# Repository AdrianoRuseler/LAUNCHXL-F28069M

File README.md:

# LAUNCHXL-F28069M

## C2000 Delfino MCUs F28069M LaunchPad Development Kit 
http://www.ti.com/tool/LAUNCHXL-F28069M

## TMS320F28069M
http://www.ti.com/product/TMS320F28069M/technicaldocuments

## Code Composer Studio IDE 
http://www.ti.com/tool/ccstudio

## controlSUITE 
http://www.ti.com/tool/controlsuite

## Wiki
https://aws.adrianoruseler.com/wiki/index.php/LAUNCHXL-F28069M

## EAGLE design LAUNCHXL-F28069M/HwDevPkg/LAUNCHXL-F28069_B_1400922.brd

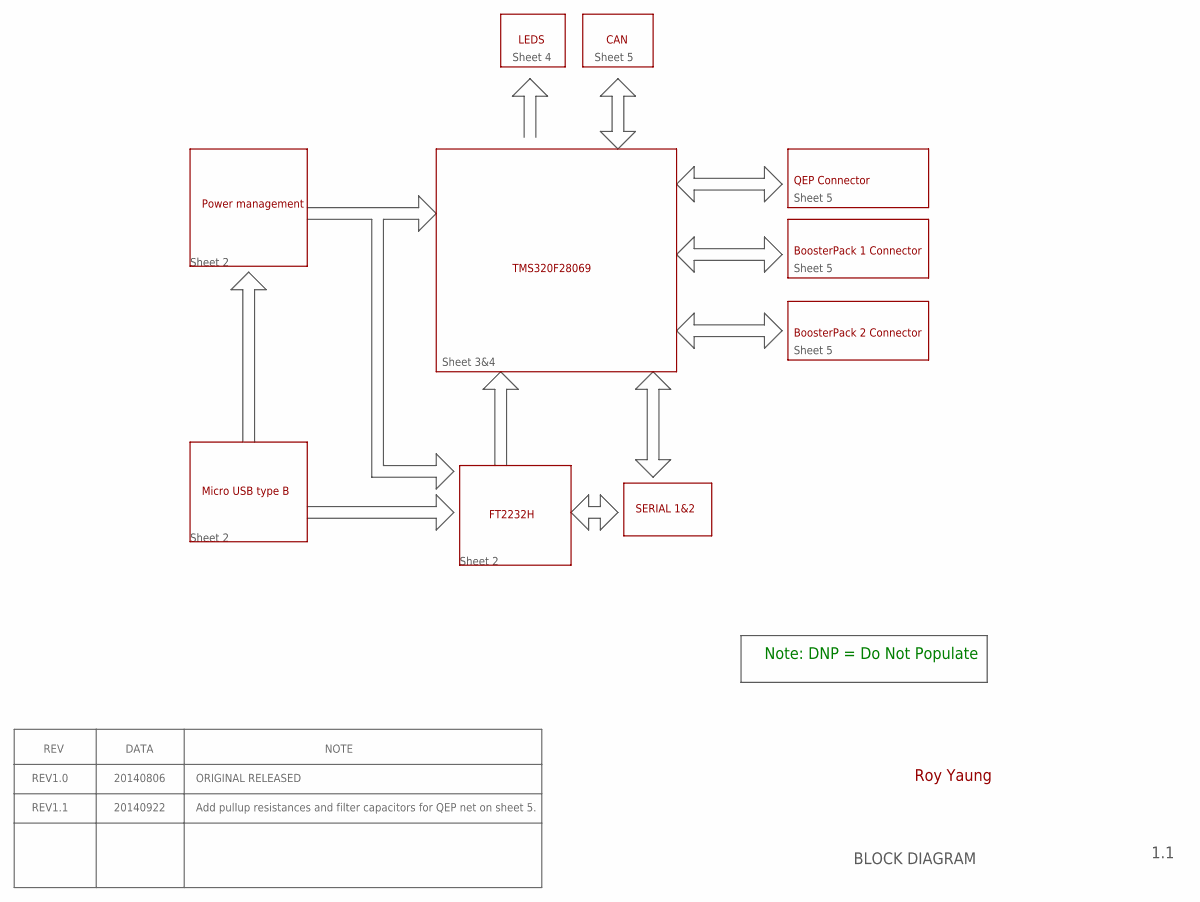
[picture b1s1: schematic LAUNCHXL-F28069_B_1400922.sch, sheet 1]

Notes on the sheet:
1.1
BLOCK DIAGRAM
Power management
Micro USB type B
FT2232H
TMS320F28069
BoosterPack 1 Connector
LEDS
CAN
SERIAL 1&2
Sheet 2
Sheet 3&4
BoosterPack 2 Connector
QEP Connector
Note: DNP = Do Not Populate
Roy Yaung
Sheet 5
Sheet 4
REV
DATA
NOTE
REV1.0
REV1.1
20140806
20140922
ORIGINAL RELEASED
Add pullup resistances and filter capacitors for QEP net on sheet 5.

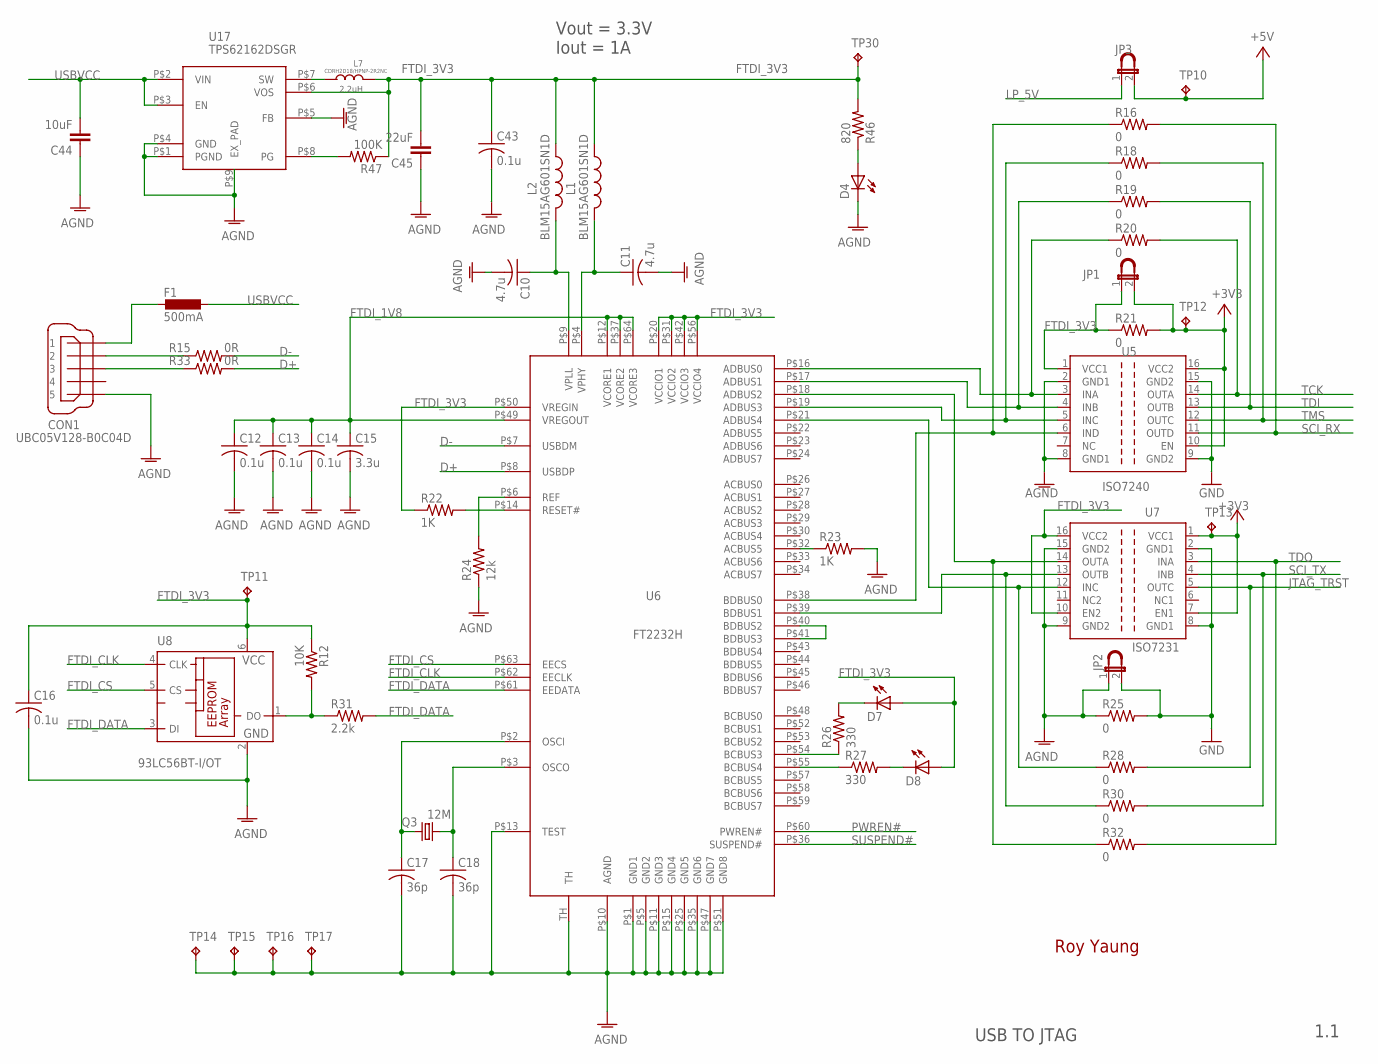
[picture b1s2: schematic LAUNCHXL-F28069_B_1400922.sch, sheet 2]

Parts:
C10, C11: 4.7u; C0402
C12, C13, C14, C16, C43: 0.1u; C0402
C15: 3.3u; C0402
C17, C18: 36p; C0402
C44: 10uF; SPARKFUN_1210
C45: 22uF; SPARKFUN_1210
CON1: UBC05V128-B0C04D; 32005-201
D4, D7, D8: LEDCHIP-LED0603; CHIP-LED0603
F1: 500mA; L1812
JP1, JP2, JP3: JP1ENORM; JP1
L1, L2: BLM15AG601SN1D; R0402
L7: 2.2uH; INDUCT-3.2*3.2
Q3: 12M; HC49UP
R12: 10K; R0402
R15, R33: 0R; R0402
R16, R18, R19, R20, R21, R25, R28, R30, R32: 0; R1206
R22, R23: 1K; R0402
R24: 12k; R0402
R26, R27: 330; R0402
R31: 2.2k; R0402
R46: 820; R0402
R47: 100K; R0402
TP10, TP11, TP12, TP13, TP14, TP15, TP16, TP17, TP30: TESTPAD_TPB1,27; TESTPAD_B1,27
U5: ISO7240; SO-16DW
U6: FT2232H; QFN64
U7: ISO7231; SO-16DW
U8: 93LC56BT-I/OT; SOT23-6
U17: TPS62162DSGR; TI_DSG8
U$9, U$10, U$11: ROY_JUMPER

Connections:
+3V3: JP1.2, R21.2, TP12.TP, TP13.TP, U5.10 (EN), U5.16 (VCC2), U7.1 (VCC1), U7.7 (EN1); also elsewhere on the board
+5V: JP3.2, TP10.TP; also elsewhere on the board
AGND: C10.2, C11.2, C12.2, C13.2, C14.2, C15.2, C16.2, C17.2, C18.2, C43.2, C44.1, C45.1, CON1.5, D4.C, JP2.1, R23.2, R24.1, R25.1, TP14.TP, TP15.TP, TP16.TP, TP17.TP, U5.2 (GND1), U5.8 (GND1), U6.P$1 (GND1), U6.P$5 (GND2), U6.P$10 (AGND), U6.P$11 (GND3), U6.P$13 (TEST), U6.P$15 (GND4), U6.P$25 (GND5), U6.P$35 (GND6), U6.P$47 (GND7), U6.P$51 (GND8), U6.TH, U7.9 (GND2), U7.15 (GND2), U8.2 (GND), U17.P$1 (PGND), U17.P$4 (GND), U17.P$5 (FB), U17.P$9 (EX_PAD)
D+: R33.2, U6.P$8 (USBDP)
D-: R15.2, U6.P$7 (USBDM)
FTDI_1V8: C12.1, C13.1, C14.1, C15.1, U6.P$12 (VCORE1), U6.P$37 (VCORE2), U6.P$49 (VREGOUT), U6.P$64 (VCORE3)
FTDI_3V3: C16.1, C43.1, C45.2, D7.A, D8.A, JP1.1, L1.1, L2.1, L7.P$1 (1), R12.1, R21.1, R22.1, R46.2, R47.1, TP11.TP, TP30.TP, U5.1 (VCC1), U6.P$20 (VCCIO1), U6.P$31 (VCCIO2), U6.P$42 (VCCIO3), U6.P$50 (VREGIN), U6.P$56 (VCCIO4), U7.10 (EN2), U7.16 (VCC2), U8.6 (VCC), U17.P$6 (VOS)
FTDI_CLK: U6.P$62 (EECLK), U8.4 (CLK)
FTDI_CS: U6.P$63 (EECS), U8.5 (CS)
FTDI_DATA: R31.2, U6.P$61 (EEDATA), U8.3 (DI)
GND: JP2.2, R25.2, U5.9 (GND2), U5.15 (GND2), U7.2 (GND1), U7.8 (GND1); also elsewhere on the board
JTAG_TRST: R28.2, U7.5 (OUTC); also elsewhere on the board
LP_5V: JP3.1; also elsewhere on the board
unnamed: R20.1, U5.3 (INA), U6.P$16 (ADBUS0)
unnamed: C17.1, Q3.1, U6.P$2 (OSCI)
unnamed: R19.1, U5.4 (INB), U6.P$17 (ADBUS1)
unnamed: R32.1, U6.P$18 (ADBUS2), U7.14 (OUTA)
unnamed: R18.1, U5.5 (INC), U6.P$19 (ADBUS3)
unnamed: C18.1, Q3.2, U6.P$3 (OSCO)
unnamed: R12.2, R31.1, U8.1 (DO)
unnamed: R28.1, U6.P$21 (ADBUS4), U7.12 (INC)
unnamed: R23.1, U6.P$32 (ACBUS5)
unnamed: U6.P$40 (BDBUS2), U6.P$41 (BDBUS3)
unnamed: R16.1, U5.6 (IND), U6.P$38 (BDBUS0)
unnamed: R24.2, U6.P$6 (REF)
unnamed: R26.1, U6.P$54 (BCBUS3)
unnamed: C11.1, L1.2, U6.P$4 (VPHY)
unnamed: R30.1, U6.P$39 (BDBUS1), U7.13 (OUTB)
unnamed: R27.1, U6.P$55 (BCBUS4)
unnamed: D7.C, R26.2
unnamed: D8.C, R27.2
unnamed: C10.1, L2.2, U6.P$9 (VPLL)
unnamed: R22.2, U6.P$14 (RESET#)
unnamed: CON1.2, R15.1
unnamed: CON1.3, R33.1
unnamed: D4.A, R46.1
unnamed: R47.2, U17.P$8 (PG)
unnamed: L7.P$2 (2), U17.P$7 (SW)
PWREN#: U6.P$60 (PWREN#)
SCI_RX: R16.2, U5.11 (OUTD); also elsewhere on the board
SCI_TX: R30.2, U7.4 (INB); also elsewhere on the board
SUSPEND#: U6.P$36 (SUSPEND#)
TCK: R20.2, U5.14 (OUTA); also elsewhere on the board
TDI: R19.2, U5.13 (OUTB); also elsewhere on the board
TDO: R32.2, U7.3 (INA); also elsewhere on the board
TMS: R18.2, U5.12 (OUTC); also elsewhere on the board
USBVCC: C44.2, F1.1, U17.P$2 (VIN), U17.P$3 (EN)
XUSB: CON1.1, F1.2

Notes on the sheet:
1.1
USB TO JTAG
Roy Yaung
Vout = 3.3V
Iout = 1A
CDRH2D18/HPNP-2R2NC

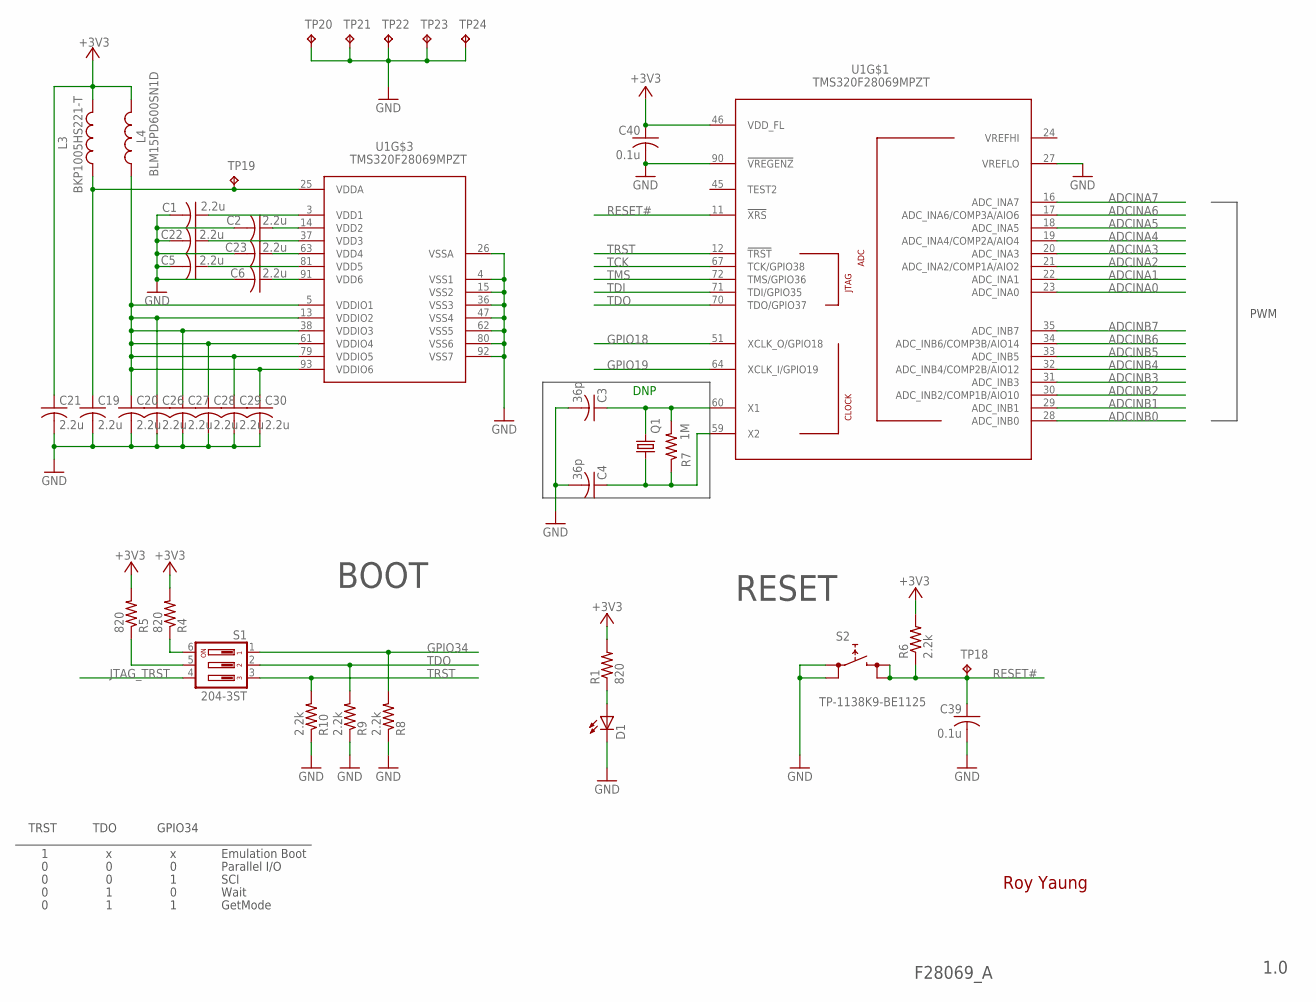
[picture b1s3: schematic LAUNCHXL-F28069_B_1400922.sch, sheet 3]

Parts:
C1, C2, C5, C6, C19, C20, C21, C22, C23, C26, C27, C28, C29, C30: 2.2u; C0402
C3, C4: 36p; C0402
C39, C40: 0.1u; C0402
D1: LEDCHIP-LED0603; CHIP-LED0603
L3: BKP1005HS221-T; R0402
L4: BLM15PD600SN1D; R0402
Q1: CRYSTALHC49S; HC49/S
R1, R4, R5: 820; R0402
R6, R8, R9, R10: 2.2k; R0402
R7: 1M; R0402
S1: 204-3ST; CTS-219-03
S2: TP-1138K9-BE1125; FSMJSMA
TP18, TP19, TP20, TP21, TP22, TP23, TP24: TESTPAD_TPB1,27; TESTPAD_B1,27
U1: TMS320F28069MPZT; PQFP100

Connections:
+3V3: C21.1, C40.1, L3.2, L4.2, R1.2, R4.2, R5.2, R6.2, U1.46 (VDD_FL); also elsewhere on the board
ADCINA0: U1.23 (ADC_INA0); also elsewhere on the board
ADCINA1: U1.22 (ADC_INA1); also elsewhere on the board
ADCINA2: U1.21 (ADC_INA2/COMP1A/AIO2); also elsewhere on the board
ADCINA3: U1.20 (ADC_INA3); also elsewhere on the board
ADCINA4: U1.19 (ADC_INA4/COMP2A/AIO4); also elsewhere on the board
ADCINA5: U1.18 (ADC_INA5); also elsewhere on the board
ADCINA6: U1.17 (ADC_INA6/COMP3A/AIO6); also elsewhere on the board
ADCINA7: U1.16 (ADC_INA7); also elsewhere on the board
ADCINB0: U1.28 (ADC_INB0); also elsewhere on the board
ADCINB1: U1.29 (ADC_INB1); also elsewhere on the board
ADCINB2: U1.30 (ADC_INB2/COMP1B/AIO10); also elsewhere on the board
ADCINB3: U1.31 (ADC_INB3); also elsewhere on the board
ADCINB4: U1.32 (ADC_INB4/COMP2B/AIO12); also elsewhere on the board
ADCINB5: U1.33 (ADC_INB5); also elsewhere on the board
ADCINB6: U1.34 (ADC_INB6/COMP3B/AIO14); also elsewhere on the board
ADCINB7: U1.35 (ADC_INB7); also elsewhere on the board
GND: C1.2, C2.2, C3.2, C4.2, C5.2, C6.2, C19.2, C20.2, C21.2, C22.2, C23.2, C26.2, C27.2, C28.2, C29.2, C30.2, C39.2, C40.2, D1.C, R8.1, R9.1, R10.1, S2.P$1 (0), S2.P$2 (0), TP20.TP, TP21.TP, TP22.TP, TP23.TP, TP24.TP, U1.4 (VSS1), U1.15 (VSS2), U1.26 (VSSA), U1.27 (VREFLO), U1.36 (VSS3), U1.47 (VSS4), U1.62 (VSS5), U1.80 (VSS6), U1.90 (!VREGENZ), U1.92 (VSS7); also elsewhere on the board
GPIO18: U1.51 (XCLK_O/GPIO18); also elsewhere on the board
GPIO19: U1.64 (XCLK_I/GPIO19); also elsewhere on the board
GPIO34: R8.2, S1.1; also elsewhere on the board
JTAG_TRST: S1.4; also elsewhere on the board
unnamed: C3.1, Q1.2, R7.2, U1.60 (X1)
unnamed: R4.1, S1.6
unnamed: R5.1, S1.5
unnamed: C4.1, Q1.1, R7.1, U1.59 (X2)
unnamed: D1.A, R1.1
unnamed: C1.1, U1.3 (VDD1)
unnamed: C2.1, U1.14 (VDD2)
unnamed: C22.1, U1.37 (VDD3)
unnamed: C23.1, U1.63 (VDD4)
unnamed: C5.1, U1.81 (VDD5)
unnamed: C6.1, U1.91 (VDD6)
RESET#: C39.1, R6.1, S2.P$3 (1), S2.P$4 (1), TP18.TP, U1.11 (!XRS); also elsewhere on the board
TCK: U1.67 (TCK/GPIO38); also elsewhere on the board
TDI: U1.71 (TDI/GPIO35); also elsewhere on the board
TDO: R9.2, S1.2, U1.70 (TDO/GPIO37); also elsewhere on the board
TMS: U1.72 (TMS/GPIO36); also elsewhere on the board
TRST: R10.2, S1.3, U1.12 (!TRST)
VDDA: C19.1, L3.1, TP19.TP, U1.25 (VDDA)
VDDIO: C20.1, C26.1, C27.1, C28.1, C29.1, C30.1, L4.1, U1.5 (VDDIO1), U1.13 (VDDIO2), U1.38 (VDDIO3), U1.61 (VDDIO4), U1.79 (VDDIO5), U1.93 (VDDIO6)

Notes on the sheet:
1.0
F28069_A
PWM
TDO
GPIO34
TRST
Emulation Boot
Parallel I/O
SCI
Wait
GetMode
RESET
BOOT
DNP
Roy Yaung

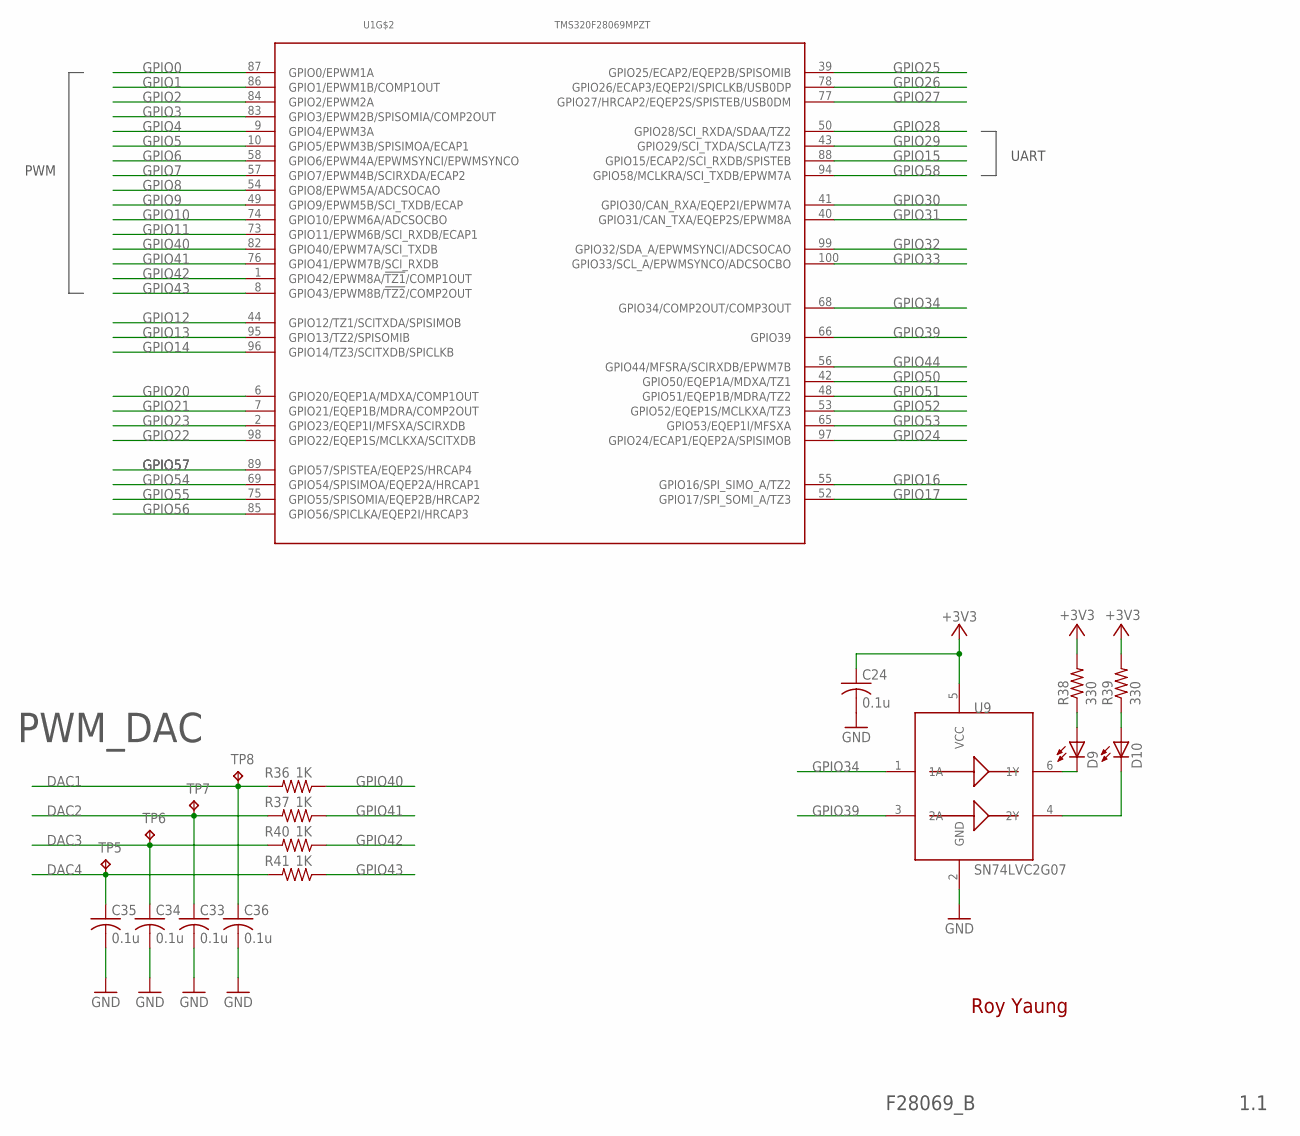
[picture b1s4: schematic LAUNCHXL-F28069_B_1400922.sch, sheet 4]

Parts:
C24, C33, C34, C35, C36: 0.1u; C0402
D9, D10: LEDCHIP-LED0603; CHIP-LED0603
R36, R37, R40, R41: 1K; R0402
R38, R39: 330; R0402
TP5, TP6, TP7, TP8: TESTPAD_TPB1,27; TESTPAD_B1,27
U1: TMS320F28069MPZT; PQFP100
U9: SN74LVC2G07; SOT23-6-DBV

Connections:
+3V3: C24.1, R38.2, R39.2, U9.5 (VCC); also elsewhere on the board
DAC1: C36.1, R36.2, TP8.TP; also elsewhere on the board
DAC2: C33.1, R37.2, TP7.TP; also elsewhere on the board
DAC3: C34.1, R40.2, TP6.TP; also elsewhere on the board
DAC4: C35.1, R41.2, TP5.TP; also elsewhere on the board
GND: C24.2, C33.2, C34.2, C35.2, C36.2, U9.2 (GND); also elsewhere on the board
GPIO0: U1.87 (GPIO0/EPWM1A); also elsewhere on the board
GPIO1: U1.86 (GPIO1/EPWM1B/COMP1OUT); also elsewhere on the board
GPIO2: U1.84 (GPIO2/EPWM2A); also elsewhere on the board
GPIO3: U1.83 (GPIO3/EPWM2B/SPISOMIA/COMP2OUT); also elsewhere on the board
GPIO4: U1.9 (GPIO4/EPWM3A); also elsewhere on the board
GPIO5: U1.10 (GPIO5/EPWM3B/SPISIMOA/ECAP1); also elsewhere on the board
GPIO6: U1.58 (GPIO6/EPWM4A/EPWMSYNCI/EPWMSYNCO); also elsewhere on the board
GPIO7: U1.57 (GPIO7/EPWM4B/SCIRXDA/ECAP2); also elsewhere on the board
GPIO8: U1.54 (GPIO8/EPWM5A/ADCSOCAO); also elsewhere on the board
GPIO9: U1.49 (GPIO9/EPWM5B/SCI_TXDB/ECAP); also elsewhere on the board
GPIO10: U1.74 (GPIO10/EPWM6A/ADCSOCBO); also elsewhere on the board
GPIO11: U1.73 (GPIO11/EPWM6B/SCI_RXDB/ECAP1); also elsewhere on the board
GPIO12: U1.44 (GPIO12/TZ1/SCITXDA/SPISIMOB); also elsewhere on the board
GPIO13: U1.95 (GPIO13/TZ2/SPISOMIB); also elsewhere on the board
GPIO14: U1.96 (GPIO14/TZ3/SCITXDB/SPICLKB); also elsewhere on the board
GPIO15: U1.88 (GPIO15/ECAP2/SCI_RXDB/SPISTEB); also elsewhere on the board
GPIO16: U1.55 (GPIO16/SPI_SIMO_A/TZ2); also elsewhere on the board
GPIO17: U1.52 (GPIO17/SPI_SOMI_A/TZ3); also elsewhere on the board
GPIO20: U1.6 (GPIO20/EQEP1A/MDXA/COMP1OUT); also elsewhere on the board
GPIO21: U1.7 (GPIO21/EQEP1B/MDRA/COMP2OUT); also elsewhere on the board
GPIO22: U1.98 (GPIO22/EQEP1S/MCLKXA/SCITXDB); also elsewhere on the board
GPIO23: U1.2 (GPIO23/EQEP1I/MFSXA/SCIRXDB); also elsewhere on the board
GPIO24: U1.97 (GPIO24/ECAP1/EQEP2A/SPISIMOB); also elsewhere on the board
GPIO25: U1.39 (GPIO25/ECAP2/EQEP2B/SPISOMIB); also elsewhere on the board
GPIO26: U1.78 (GPIO26/ECAP3/EQEP2I/SPICLKB/USB0DP); also elsewhere on the board
GPIO27: U1.77 (GPIO27/HRCAP2/EQEP2S/SPISTEB/USB0DM); also elsewhere on the board
GPIO28: U1.50 (GPIO28/SCI_RXDA/SDAA/TZ2); also elsewhere on the board
GPIO29: U1.43 (GPIO29/SCI_TXDA/SCLA/TZ3); also elsewhere on the board
GPIO30: U1.41 (GPIO30/CAN_RXA/EQEP2I/EPWM7A); also elsewhere on the board
GPIO31: U1.40 (GPIO31/CAN_TXA/EQEP2S/EPWM8A); also elsewhere on the board
GPIO32: U1.99 (GPIO32/SDA_A/EPWMSYNCI/ADCSOCAO); also elsewhere on the board
GPIO33: U1.100 (GPIO33/SCL_A/EPWMSYNCO/ADCSOCBO); also elsewhere on the board
GPIO34: U1.68 (GPIO34/COMP2OUT/COMP3OUT), U9.1 (1A); also elsewhere on the board
GPIO39: U1.66 (GPIO39), U9.3 (2A)
GPIO40: R36.1, U1.82 (GPIO40/EPWM7A/SCI_TXDB)
GPIO41: R37.1, U1.76 (GPIO41/EPWM7B/SCI_RXDB)
GPIO42: R40.1, U1.1 (GPIO42/EPWM8A/!TZ1!/COMP1OUT)
GPIO43: R41.1, U1.8 (GPIO43/EPWM8B/!TZ2!/COMP2OUT)
GPIO44: U1.56 (GPIO44/MFSRA/SCIRXDB/EPWM7B); also elsewhere on the board
GPIO50: U1.42 (GPIO50/EQEP1A/MDXA/TZ1); also elsewhere on the board
GPIO51: U1.48 (GPIO51/EQEP1B/MDRA/TZ2); also elsewhere on the board
GPIO52: U1.53 (GPIO52/EQEP1S/MCLKXA/TZ3); also elsewhere on the board
GPIO53: U1.65 (GPIO53/EQEP1I/MFSXA); also elsewhere on the board
GPIO54: U1.69 (GPIO54/SPISIMOA/EQEP2A/HRCAP1); also elsewhere on the board
GPIO55: U1.75 (GPIO55/SPISOMIA/EQEP2B/HRCAP2); also elsewhere on the board
GPIO56: U1.85 (GPIO56/SPICLKA/EQEP2I/HRCAP3); also elsewhere on the board
GPIO57: U1.89 (GPIO57/SPISTEA/EQEP2S/HRCAP4)
GPIO58: U1.94 (GPIO58/MCLKRA/SCI_TXDB/EPWM7A); also elsewhere on the board
unnamed: D9.C, U9.6 (1Y)
unnamed: D9.A, R38.1
unnamed: D10.A, R39.1
unnamed: D10.C, U9.4 (2Y)

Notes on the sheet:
1.1
F28069_B
PWM
UART
PWM_DAC
Roy Yaung

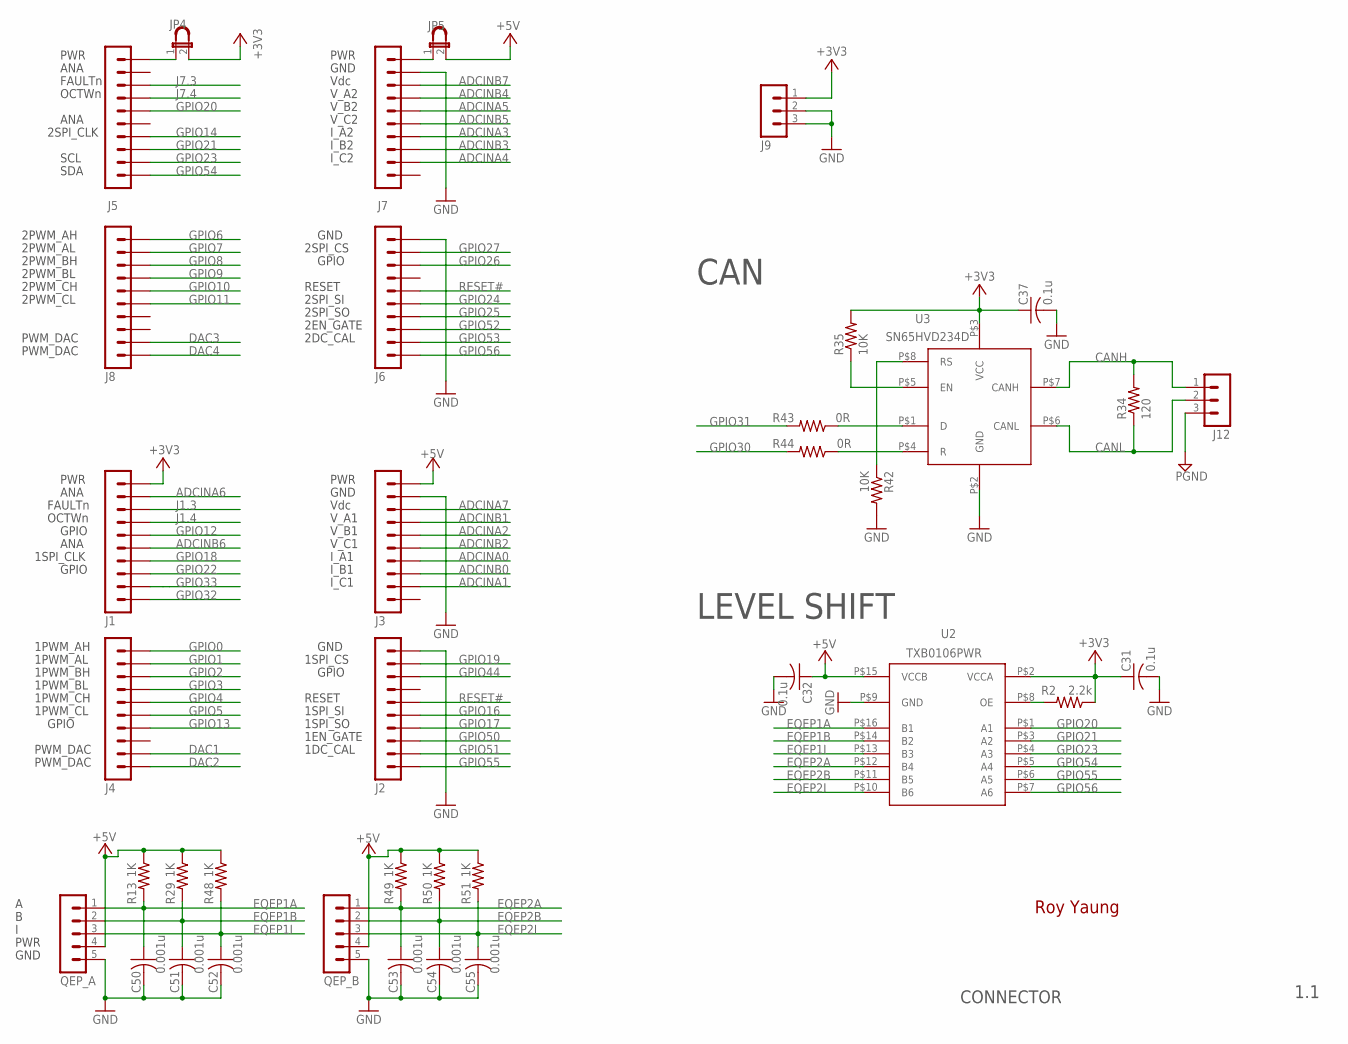
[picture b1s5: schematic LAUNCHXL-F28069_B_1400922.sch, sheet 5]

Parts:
C31, C32, C37: 0.1u; C0402
C50, C51, C52, C53, C54, C55: 0.001u; C0402
J1, J2, J3, J4, J5, J6, J7, J8: MA10-1
J9: CON-LSTB_MA03-1
J12: MA03-1
JP4, JP5: JP1ENORM; JP1
QEP_A: MA05-1
QEP_B: MA05-1
R2: 2.2k; R0402
R13, R29, R48, R49, R50, R51: 1K; R0402
R34: 120; R0402
R35, R42: 10K; R0402
R43, R44: 0R; R0402
U2: TXB0106PWR; TSSOP16-PW
U3: SN65HVD234D; SOIC8-PDSO
U$12, U$13: ROY_JUMPER

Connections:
+3V3: C31.1, C37.1, J1.1, J9.1, JP4.2, R2.1, R35.2, U2.P$2 (VCCA), U3.P$3 (VCC); also elsewhere on the board
+5V: C32.1, J3.1, JP5.2, QEP_A.4, QEP_B.4, R13.1, R29.1, R48.1, R49.1, R50.1, R51.1, U2.P$15 (VCCB); also elsewhere on the board
ADCINA0: J3.7; also elsewhere on the board
ADCINA1: J3.9; also elsewhere on the board
ADCINA2: J3.5; also elsewhere on the board
ADCINA3: J7.7; also elsewhere on the board
ADCINA4: J7.9; also elsewhere on the board
ADCINA5: J7.5; also elsewhere on the board
ADCINA6: J1.2; also elsewhere on the board
ADCINA7: J3.3; also elsewhere on the board
ADCINB0: J3.8; also elsewhere on the board
ADCINB1: J3.4; also elsewhere on the board
ADCINB2: J3.6; also elsewhere on the board
ADCINB3: J7.8; also elsewhere on the board
ADCINB4: J7.4; also elsewhere on the board
ADCINB5: J7.6; also elsewhere on the board
ADCINB6: J1.6; also elsewhere on the board
ADCINB7: J7.3; also elsewhere on the board
CANH: J12.1, R34.2, U3.P$7 (CANH)
CANL: J12.2, R34.1, U3.P$6 (CANL)
DAC1: J4.9; also elsewhere on the board
DAC2: J4.10; also elsewhere on the board
DAC3: J8.9; also elsewhere on the board
DAC4: J8.10; also elsewhere on the board
EQEP1A: C50.1, QEP_A.1, R13.2, U2.P$16 (B1)
EQEP1B: C51.1, QEP_A.2, R29.2, U2.P$14 (B2)
EQEP1I: C52.1, QEP_A.3, R48.2, U2.P$13 (B3)
EQEP2A: C53.1, QEP_B.1, R49.2, U2.P$12 (B4)
EQEP2B: C54.1, QEP_B.2, R50.2, U2.P$11 (B5)
EQEP2I: C55.1, QEP_B.3, R51.2, U2.P$10 (B6)
GND: C31.2, C32.2, C37.2, C50.2, C51.2, C52.2, C53.2, C54.2, C55.2, J2.1, J3.2, J6.1, J7.2, J9.2, J9.3, QEP_A.5, QEP_B.5, R42.2, U2.P$9 (GND), U3.P$2 (GND); also elsewhere on the board
GPIO0: J4.1; also elsewhere on the board
GPIO1: J4.2; also elsewhere on the board
GPIO2: J4.3; also elsewhere on the board
GPIO3: J4.4; also elsewhere on the board
GPIO4: J4.5; also elsewhere on the board
GPIO5: J4.6; also elsewhere on the board
GPIO6: J8.1; also elsewhere on the board
GPIO7: J8.2; also elsewhere on the board
GPIO8: J8.3; also elsewhere on the board
GPIO9: J8.4; also elsewhere on the board
GPIO10: J8.5; also elsewhere on the board
GPIO11: J8.6; also elsewhere on the board
GPIO12: J1.5; also elsewhere on the board
GPIO13: J4.7; also elsewhere on the board
GPIO14: J5.7; also elsewhere on the board
GPIO16: J2.6; also elsewhere on the board
GPIO17: J2.7; also elsewhere on the board
GPIO18: J1.7; also elsewhere on the board
GPIO19: J2.2; also elsewhere on the board
GPIO20: J5.5, U2.P$1 (A1); also elsewhere on the board
GPIO21: J5.8, U2.P$3 (A2); also elsewhere on the board
GPIO22: J1.8; also elsewhere on the board
GPIO23: J5.9, U2.P$4 (A3); also elsewhere on the board
GPIO24: J6.6; also elsewhere on the board
GPIO25: J6.7; also elsewhere on the board
GPIO26: J6.3; also elsewhere on the board
GPIO27: J6.2; also elsewhere on the board
GPIO30: R44.2; also elsewhere on the board
GPIO31: R43.2; also elsewhere on the board
GPIO32: J1.10; also elsewhere on the board
GPIO33: J1.9; also elsewhere on the board
GPIO44: J2.3; also elsewhere on the board
GPIO50: J2.8; also elsewhere on the board
GPIO51: J2.9; also elsewhere on the board
GPIO52: J6.8; also elsewhere on the board
GPIO53: J6.9; also elsewhere on the board
GPIO54: J5.10, U2.P$5 (A4); also elsewhere on the board
GPIO55: J2.10, U2.P$6 (A5); also elsewhere on the board
GPIO56: J6.10, U2.P$7 (A6); also elsewhere on the board
J1.3: J1.3; also elsewhere on the board
J1.4: J1.4; also elsewhere on the board
J7.3: J5.3; also elsewhere on the board
J7.4: J5.4; also elsewhere on the board
unnamed: J7.1, JP5.1
unnamed: J5.1, JP4.1
unnamed: R2.2, U2.P$8 (OE)
unnamed: R35.1, U3.P$5 (EN)
unnamed: R42.1, U3.P$8 (RS)
unnamed: R43.1, U3.P$1 (D)
unnamed: R44.1, U3.P$4 (R)
RESET#: J2.5, J6.5; also elsewhere on the board

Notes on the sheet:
1.1
CONNECTOR
Vdc
V_A1
V_B1
V_C1
I_A1
I_B1
I_C1
V_A2
V_B2
V_C2
I_A2
I_B2
I_C2
PWR
ANA
FAULTn
OCTWn
GPIO
1SPI_CLK
1PWM_AH
1PWM_AL
1PWM_BH
1PWM_BL
1PWM_CH
1PWM_CL
GND
1SPI_CS
RESET
1SPI_SI
1SPI_SO
1EN_GATE
1DC_CAL
2SPI_CLK
SCL
SDA
2PWM_AH
2PWM_AL
2PWM_BH

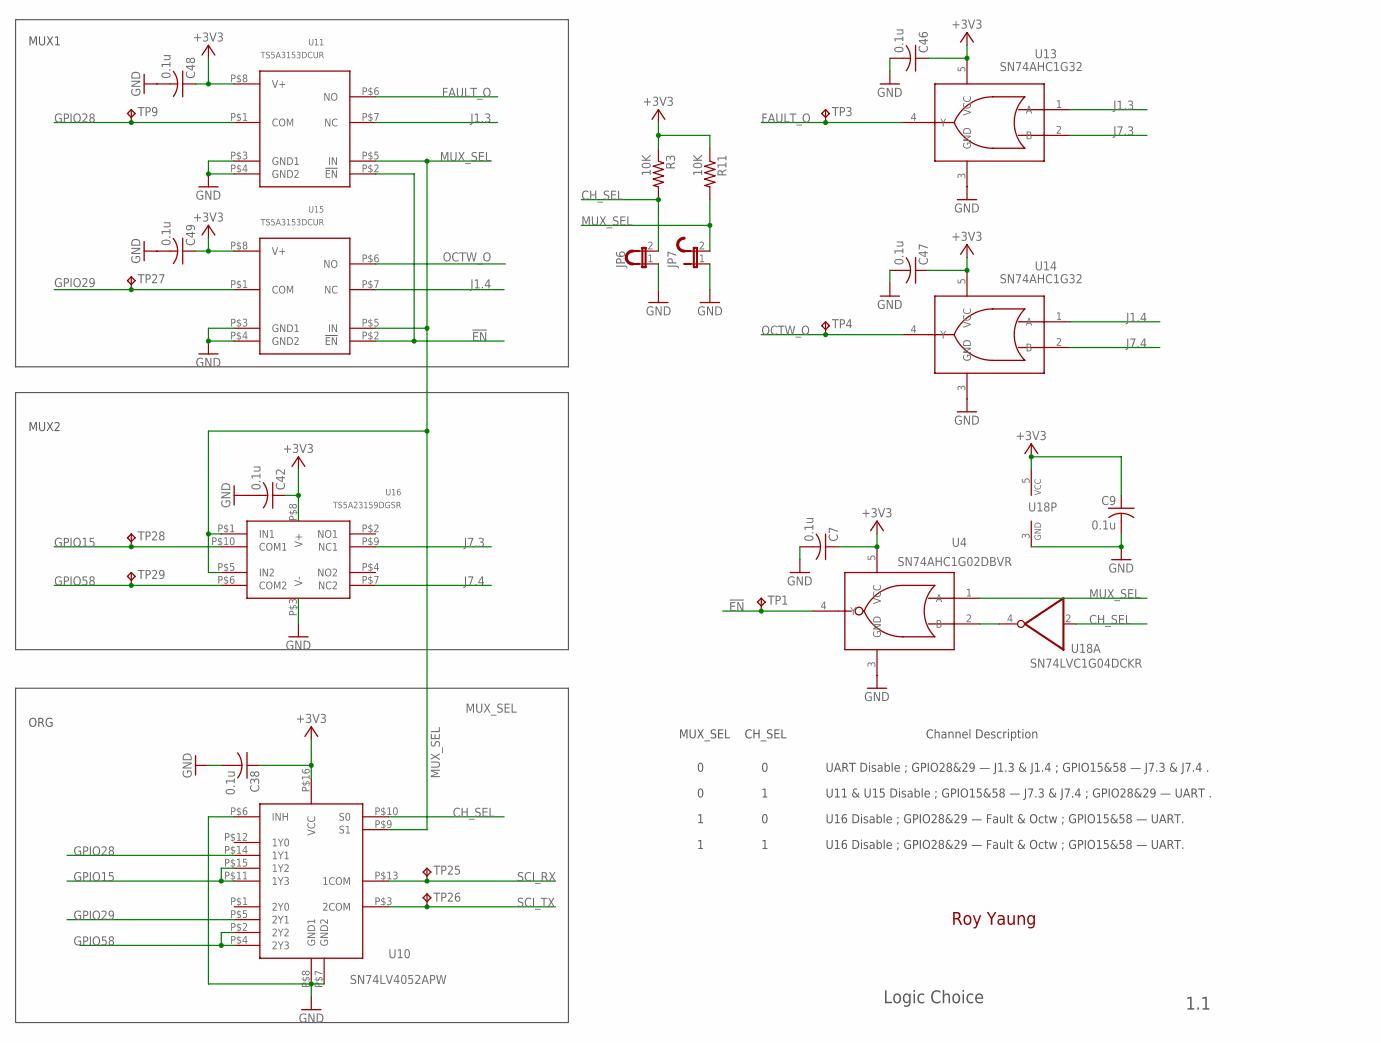
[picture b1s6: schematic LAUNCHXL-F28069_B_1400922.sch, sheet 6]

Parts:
C7, C9, C38, C42, C46, C47, C48, C49: 0.1u; C0402
JP6, JP7: JP1ENORM; JP1
R3, R11: 10K; R0402
TP1, TP3, TP4, TP9, TP25, TP26, TP27, TP28, TP29: TESTPAD_TPB1,27; TESTPAD_B1,27
U4: SN74AHC1G02DBVR; SOT23-5-DBV
U10: SN74LV4052APW; TSSOP16-PW
U11, U15: TS5A3153DCUR; TI-DCU8
U13, U14: SN74AHC1G32; SOT23-5-DBV
U16: TS5A23159DGSR; TI-DGS10
U18: SN74LVC1G04DCKR; 74XX-LITTLE-DE_SC70-5
U$1, U$2: ROY_JUMPER

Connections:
!EN: TP1.TP, U4.4 (Y), U11.P$2 (!EN), U15.P$2 (!EN)
+3V3: C7.1, C9.1, C38.1, C42.1, C46.1, C47.1, C48.1, C49.1, R3.1, R11.1, U4.5 (VCC), U10.P$16 (VCC), U11.P$8 (V+), U13.5 (VCC), U14.5 (VCC), U15.P$8 (V+), U16.P$8 (V+), U18.5 (VCC); also elsewhere on the board
CH_SEL: JP6.2, R3.2, U10.P$10 (S0), U18.2 (I)
FAULT_O: TP3.TP, U11.P$6 (NO), U13.4 (Y)
GND: C7.2, C9.2, C38.2, C42.2, C46.2, C47.2, C48.2, C49.2, JP6.1, JP7.1, U4.3 (GND), U10.P$6 (INH), U10.P$7 (GND2), U10.P$8 (GND1), U11.P$3 (GND1), U11.P$4 (GND2), U13.3 (GND), U14.3 (GND), U15.P$3 (GND1), U15.P$4 (GND2), U16.P$3 (V-), U18.3 (GND); also elsewhere on the board
GPIO15: TP28.TP, U10.P$11 (1Y3), U10.P$15 (1Y2), U16.P$10 (COM1); also elsewhere on the board
GPIO28: TP9.TP, U10.P$14 (1Y1), U11.P$1 (COM); also elsewhere on the board
GPIO29: TP27.TP, U10.P$5 (2Y1), U15.P$1 (COM); also elsewhere on the board
GPIO58: TP29.TP, U10.P$2 (2Y2), U10.P$4 (2Y3), U16.P$6 (COM2); also elsewhere on the board
J1.3: U11.P$7 (NC), U13.1 (A); also elsewhere on the board
J1.4: U14.1 (A), U15.P$7 (NC); also elsewhere on the board
J7.3: U13.2 (B), U16.P$9 (NC1); also elsewhere on the board
J7.4: U14.2 (B), U16.P$7 (NC2); also elsewhere on the board
MUX_SEL: JP7.2, R11.2, U4.1 (A), U10.P$9 (S1), U11.P$5 (IN), U15.P$5 (IN), U16.P$1 (IN1), U16.P$5 (IN2)
unnamed: U4.2 (B), U18.4 (O)
OCTW_O: TP4.TP, U14.4 (Y), U15.P$6 (NO)
SCI_RX: TP25.TP, U10.P$13 (1COM); also elsewhere on the board
SCI_TX: TP26.TP, U10.P$3 (2COM); also elsewhere on the board

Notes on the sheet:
1.1
Logic Choice
Roy Yaung
MUX_SEL
CH_SEL
UART Disable ; GPIO28&29 — J1.3 & J1.4 ; GPIO15&58 — J7.3 & J7.4 .
U11 & U15 Disable ; GPIO15&58 — J7.3 & J7.4 ; GPIO28&29 — UART .
Channel Description
U16 Disable ; GPIO28&29 — Fault & Octw ; GPIO15&58 — UART.
MUX2
MUX1
ORG

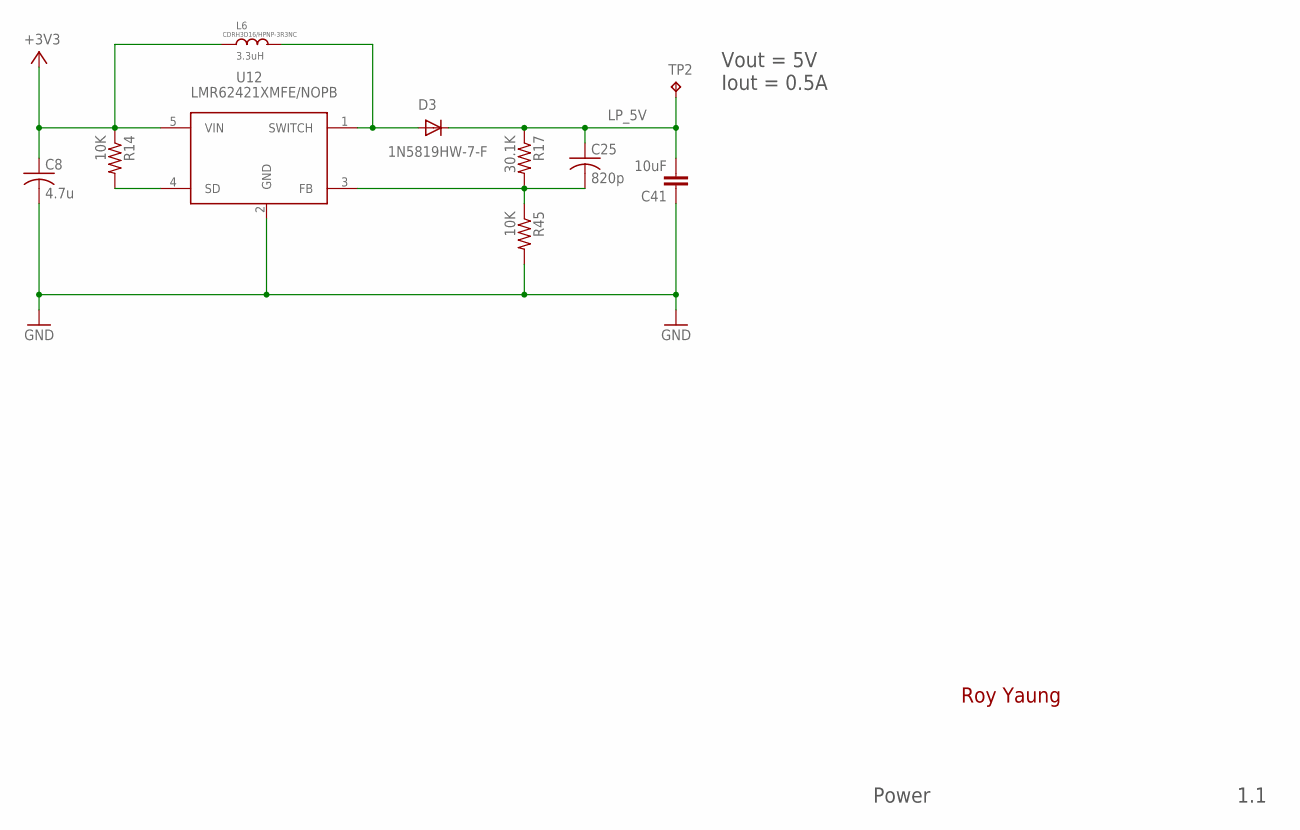
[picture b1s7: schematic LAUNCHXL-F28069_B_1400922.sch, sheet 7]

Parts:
C8: 4.7u; C0402
C25: 820p; C0402
C41: 10uF; SPARKFUN_1210
D3: 1N5819HW-7-F; SOD123
L6: 3.3uH; INDUCT-3_7*3_5
R14, R45: 10K; R0402
R17: 30.1K; R0402
TP2: TESTPAD_TPB1,27; TESTPAD_B1,27
U12: LMR62421XMFE/NOPB; SOT23-5-DBV

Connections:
+3V3: C8.1, L6.P$1 (1), R14.1, U12.5 (VIN); also elsewhere on the board
GND: C8.2, C41.1, R45.2, U12.2 (GND); also elsewhere on the board
LP_5V: C25.1, C41.2, D3.C, R17.1, TP2.TP; also elsewhere on the board
unnamed: R14.2, U12.4 (SD)
unnamed: D3.A, L6.P$2 (2), U12.1 (SWITCH)
unnamed: C25.2, R17.2, R45.1, U12.3 (FB)

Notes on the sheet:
1.1
Power
Roy Yaung
Vout = 5V
Iout = 0.5A
CDRH3D16/HPNP-3R3NC

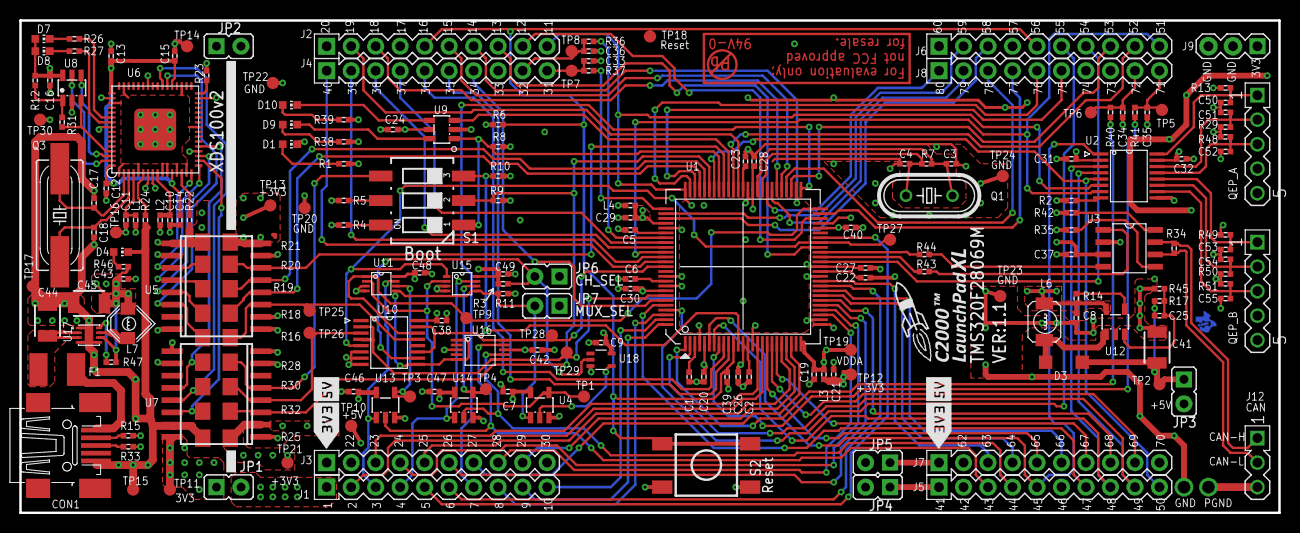
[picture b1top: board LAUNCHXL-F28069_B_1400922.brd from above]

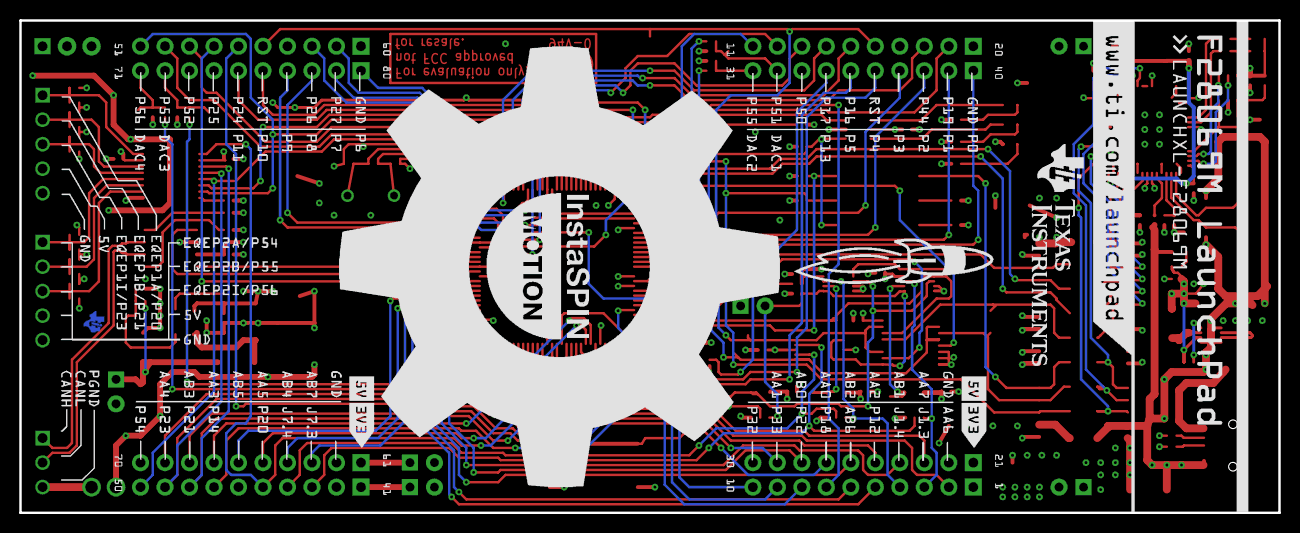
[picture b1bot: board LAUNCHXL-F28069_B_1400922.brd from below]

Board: 4 copper layers, 130.6 x 51.1 mm, 214 parts (2 on the bottom side), 162 nets.

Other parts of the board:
E$1: IS_MOTION
E$2: F28069M_BACKSILK_1
E$3: F28069M_BACKSILK_2
E$4: F28069M_BACKSILK_3
E$5, E$6: POWER_TAG_FRONT
E$7, E$8: POWERTAG_BACK
E$9: ROCKET_1
U$3: MSP430_LAB_TILOGO_SMALL
U$4: TRADEMARK
U$5: STI_LOGO_ROCKET
U$6: STI_LOGO_LAUNCHPADC2K
U$7: XL
U$8: MSP430_LAB_TILOGO_SMALL_TSTOP

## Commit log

2016-07-03 :lollipop: Added .gitattributes & .gitignore files
2016-07-03 Added ControlSUITE files
    Added ControlSUITE files
2016-07-04 Added some examples
    Added some examples from controlSUITE v151
2016-08-23 Adicionado exemplo pisca LED
2016-08-23 Adicionado função que copia para RAM na gravação em FLASH
2016-08-23 wt funcionando porém senos e cossenos não;
